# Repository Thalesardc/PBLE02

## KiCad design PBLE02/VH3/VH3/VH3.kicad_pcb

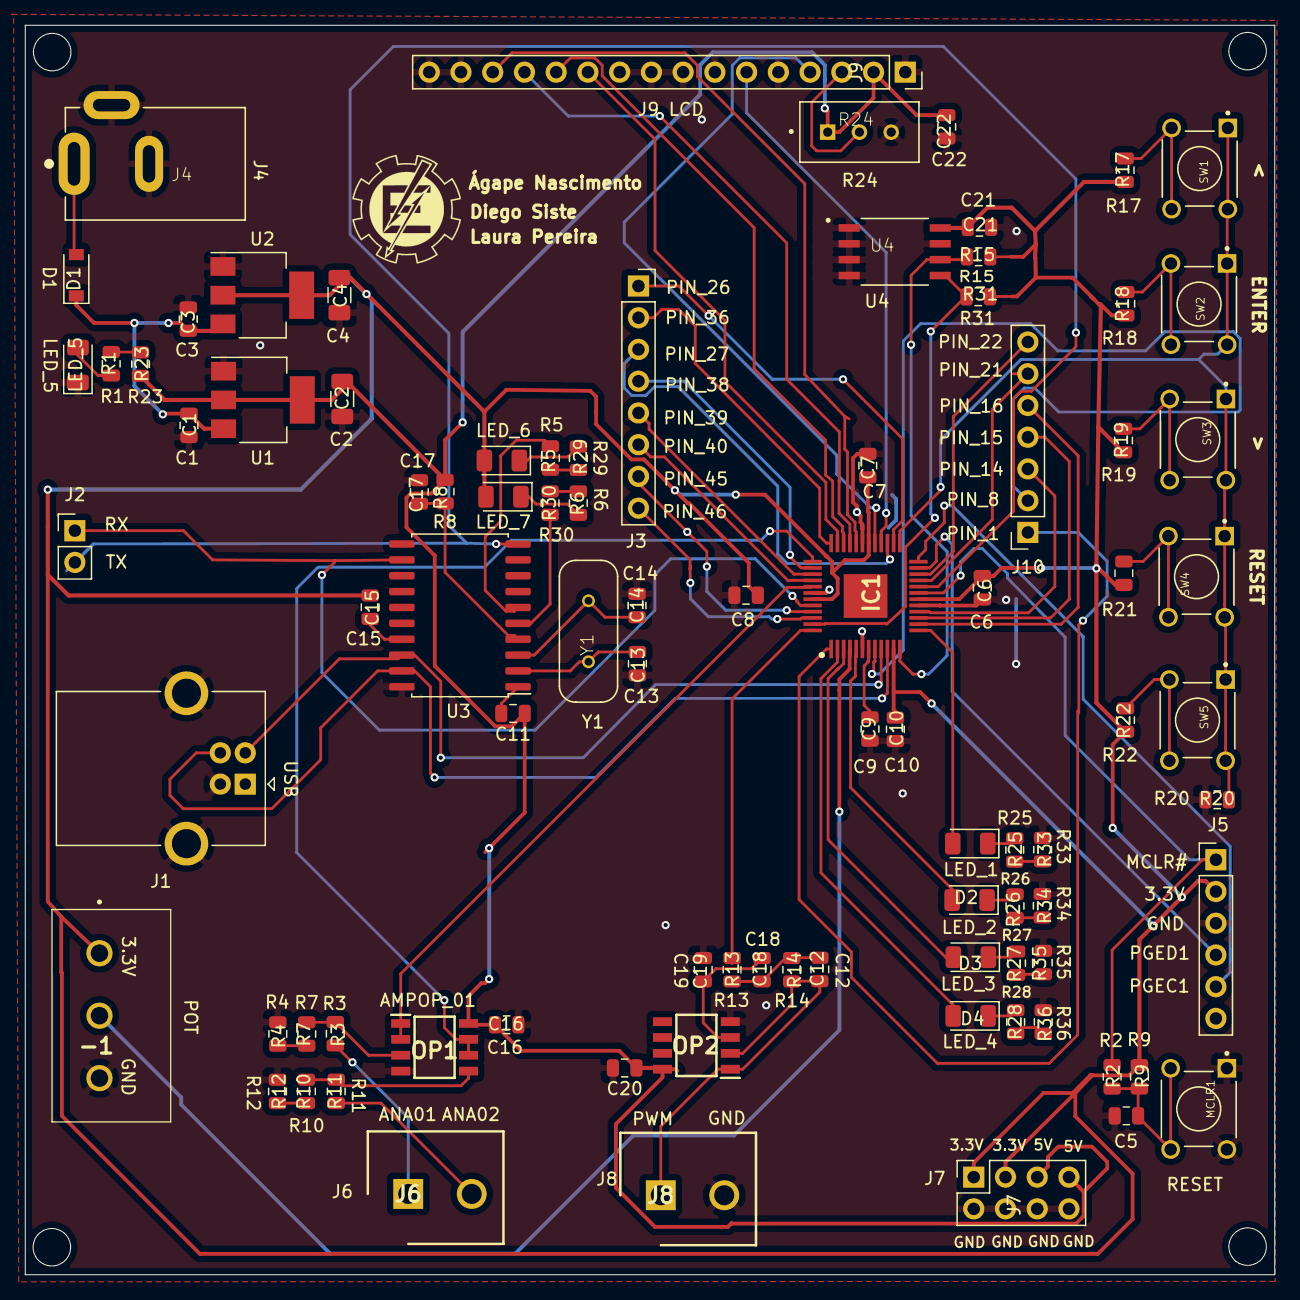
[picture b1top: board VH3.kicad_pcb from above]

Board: 2 copper layers, 100.0 x 100.0 mm, 90 parts (0 on the bottom side), 82 nets.

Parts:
-1: POT; P160KN0QD15B10K
C1, C3, C5, C6, C7, C8, C10, C11, C15, C16, C17, C20, C21, C22: 100nF; C_0805_2012Metric
C2, C4: 10uF; C_1206_3216Metric
C9: 10uF; C_0805_2012Metric
C12, C18, C19: 220nF; C_0805_2012Metric
C13, C14: 22pF; C_0805_2012Metric
D1: 1N5819; D_SOD-123
D2: LED_2; LED_1206_3216Metric
D3: LED_3; LED_1206_3216Metric
D4: LED_4; LED_1206_3216Metric
IC1: PIC32MM0064GPM048-I_PT; QFP50P900X900X120-49N
J1: USB_B; USB_B_OST_USB-B1HSxx_Horizontal
J2: Conn_01x02; PinHeader_1x02_P2.54mm_Vertical
J3: EXTENSÃO_2; PinSocket_1x08_P2.54mm_Vertical
J4: PJ-002A; CUI_PJ-002A
J5: ICSP; PinHeader_1x06_P2.54mm_Vertical
J6, J8: OSTTA024163; SHDR2W100P0X508_1X2_1086X900X1300P
J7: Conn_02x04_Top_Bottom; PinSocket_2x04_P2.54mm_Vertical
J9: LDC_header; PinSocket_1x16_P2.54mm_Vertical
J10: EXTENSÃO_1; PinSocket_1x07_P2.54mm_Vertical
LED_1: LED_1; LED_1206_3216Metric
LED_5: LED_ALIM; LED_1206_3216Metric
LED_6: Lx_LED; LED_1206_3216Metric
LED_7: Rx_LED; LED_1206_3216Metric
MCLR1: SWL1; SW_1825910-6-4
OP1, OP2: LM358DG; SOIC127P600X175-8N
R1, R29, R30, R33, R34, R35, R36: 56; R_0805_2012Metric
R2, R22: 1k; R_0805_2012Metric
R3, R4, R7, R10, R11, R12, R21: 3k3; R_0805_2012Metric
R5, R6, R13, R14, R23, R25, R26, R27, R28: 100; R_0805_2012Metric
R8, R15, R19, R31: 4k7; R_0805_2012Metric
R9, R20: 10k; R_0805_2012Metric
R17: 9k1; R_0805_2012Metric
R18: 6k8; R_0805_2012Metric
R24: POT_LCD; TRIM_3296W-1-103RLF
SW1, SW2, SW3, SW4, SW5: 1825910-6; SW_1825910-6-4
U1: LD1117DT50TR_SOT223; SOT-223-3_TabPin2
U2: LD1117S33CTR_SOT223; SOT-223-3_TabPin2
U3: MCP2200-I-SO; SOIC-20W_7.5x12.8mm_P1.27mm
U4: 24LC512-I_SM; SOIC127P794X202-8N
Y1: 12MHz; XTAL_ECS-120-20-4X
ee: LOGO; unifei_logo

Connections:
+5V: C2.1, C11.1, C16.1, C20.1, C22.1, J7.5, J7.7, J9.2, OP1.8, OP2.8, R8.1, R23.2, R24.1, U1.2
AN4: IC1.37, OP1.6, OP1.7
AN11: IC1.41, OP1.1, OP1.2
D4: IC1.35, J9.11
D5: IC1.34, J9.12
D6: IC1.33, J9.13
D7: IC1.32, J9.14
D+: IC1.10, J1.3, U3.19
D-: IC1.9, J1.2, U3.18
E: IC1.28, J9.6
Earth: -1.3, C1.2, C2.2, C3.2, C4.2, C5.2, C6.2, C7.2, C8.2, C9.2, C10.2, C13.2, C14.2, C16.2, C17.2, C19.2, C20.2, C21.2, C22.2, IC1.6, IC1.17, IC1.31, IC1.42, J1.4, J1.5, J4.2, J4.3, J5.3, J7.2, J7.4, J7.6, J7.8, J8.2, J9.1, J9.5, J9.7, J9.8, J9.9, J9.10, J9.15, J9.16, LED_5.1, MCLR1.1, MCLR1.2, OP1.4, OP2.4, R4.2, R12.2, R20.2, R24.3, R33.1, R34.1, R35.1, R36.1, U1.1, U2.1, U3.20, U4.1, U4.2, U4.3, U4.4, U4.7
IN_A: OP1.3, R3.1, R7.2
IN_B: OP1.5, R10.2, R11.1
LED_1: IC1.13, LED_1.2
LED_2: D2.2, IC1.5
LED_3: D3.2, IC1.3
LED_4: D4.2, IC1.2
MCLR#: IC1.19, J5.1, R2.1
unnamed: C5.1, MCLR1.3, MCLR1.4, R2.2, R9.2
unnamed: C11.2, U3.1
unnamed: C12.1, C18.1, J8.1, OP2.1, OP2.2
unnamed: C12.2, C18.2, R13.2, R14.2
unnamed: C15.2, U3.17
unnamed: C19.1, OP2.3, R14.1
unnamed: D1.2, J4.1
unnamed: D2.1, R26.2
unnamed: D3.1, R27.2
unnamed: D4.1, R28.2
unnamed: J6.1, R7.1
unnamed: J6.2, R10.1
unnamed: J9.3, R24.2
unnamed: LED_1.1, R25.2
unnamed: LED_5.2, R1.1
unnamed: LED_6.1, R29.1
unnamed: LED_7.1, R30.1
unnamed: R1.2, R23.1
unnamed: R3.2, R4.1
unnamed: R11.2, R12.1
unnamed: R17.2, SW1.3, SW1.4
unnamed: R18.2, SW2.3, SW2.4
unnamed: R19.2, SW3.3, SW3.4
unnamed: R21.2, SW4.3, SW4.4
unnamed: R22.2, SW5.3, SW5.4
unnamed: R25.1, R33.2
unnamed: R26.1, R34.2
unnamed: R27.1, R35.2
unnamed: R28.1, R36.2
unnamed: R5.1, R29.2
unnamed: R6.1, R30.2
OSC1: C13.1, U3.2, Y1.1
OSC2: C14.1, U3.3, Y1.2
PGEC1: IC1.24, J5.5
PGED1: IC1.23, J5.4
PIN_1: IC1.1, J10.1
PIN_8: IC1.8, J10.2
PIN_14: IC1.16, J10.3
PIN_15: IC1.15, J10.4
PIN_16: IC1.14, J10.5
PIN_21: IC1.21, J10.6
PIN_22: IC1.22, J10.7
PIN_26: IC1.26, J3.1
PIN_27: IC1.27, J3.3
PIN_36: IC1.36, J3.2
PIN_38: IC1.38, J3.4
PIN_39: IC1.39, J3.5
PIN_40: IC1.40, J3.6
PIN_45: IC1.45, J3.7
PIN_46: IC1.46, J3.8
POT: -1.2, IC1.4
PWM: IC1.48, R13.1
RS: IC1.29, J9.4
RST: C17.1, R8.2, U3.4
RX: IC1.44, J2.1, U3.12
RxLED: R5.2, U3.6
SCL: IC1.12, R15.1, U4.6
SDA: IC1.47, R31.1, U4.5
TECLADO: IC1.25, R20.1, SW1.1, SW1.2, SW2.1, SW2.2, SW3.1, SW3.2, SW4.1, SW4.2, SW5.1, SW5.2
TX: IC1.20, J2.2, U3.10
TxLED: R6.2, U3.5
VCAP: C9.1, IC1.7
VUSB3V3: -1.1, C4.1, C6.1, C7.1, C8.1, C10.1, C15.1, C21.1, IC1.11, IC1.18, IC1.30, IC1.43, J5.2, J7.1, J7.3, LED_6.2, LED_7.2, R9.1, R15.2, R17.1, R18.1, R19.1, R21.1, R22.1, R31.2, U2.2, U4.8
Vin: C1.1, C3.1, D1.1, U1.3, U2.3
